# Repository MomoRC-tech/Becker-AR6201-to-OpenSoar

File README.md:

# ✈️ Wi-Fi Bridge: Glider Avionics to OpenSoar

<p align="center">
  
</p>

A small ESP32 box in the glider collects data from the cockpit instruments and sends it over Wi-Fi to OpenSoar on a phone or tablet. No cables run to the phone.

<p align="center">
<a href="docs/manual/user-manual.md"><picture><source media="(prefers-color-scheme: dark)" srcset="docs/images/nav/card-use-dark.svg"></picture></a>
<a href="docs/hardware/build-guide.md"><picture><source media="(prefers-color-scheme: dark)" srcset="docs/images/nav/card-build-dark.svg"></picture></a>
<a href="docs/README.md"><picture><source media="(prefers-color-scheme: dark)" srcset="docs/images/nav/card-reference-dark.svg"></picture></a>
</p>

---

## 1. 🎯 What it does

| Device | What you get in OpenSoar |
| --- | --- |
| 📈 Glider computer: Zander ZS1 | Flight and navigation data |
| 📡 Collision warning: Classic FLARM | Traffic and position |
| 📻 Radio: Becker AR6201 | Dedicated TCP port, verified with a bench loop. The stock OpenSoar driver is selected for the [remaining radio checks](docs/project/open-items.md#software-and-acceptance) |

Check and set it up from the phone's browser: live status per device, settings, a data monitor and a log ([web pages](docs/manual/user-manual.md#web-pages)).

<br clear="right">

---

## 2. 🚦 Status

> [!NOTE]
> **Status:** bench hardware bring-up is complete. Firmware 0.5.29 passed the hotspot phone reconnect, Becker loop and one-hour forwarding checks. [Remaining bench checks](docs/project/roadmap.md#firmware-plan)

---

## 3. ⚠️ Safety

> [!WARNING]
> Keep aircraft equipment disconnected during bench checks. Aircraft connection requires separate approval and verification of the installed wiring and radio revision. The existing installation stays untouched as a backup.

Working on the repository? Read the [work instructions](AGENTS.md) first.

---

<kbd>[⬆️ Back to top](#top)</kbd>

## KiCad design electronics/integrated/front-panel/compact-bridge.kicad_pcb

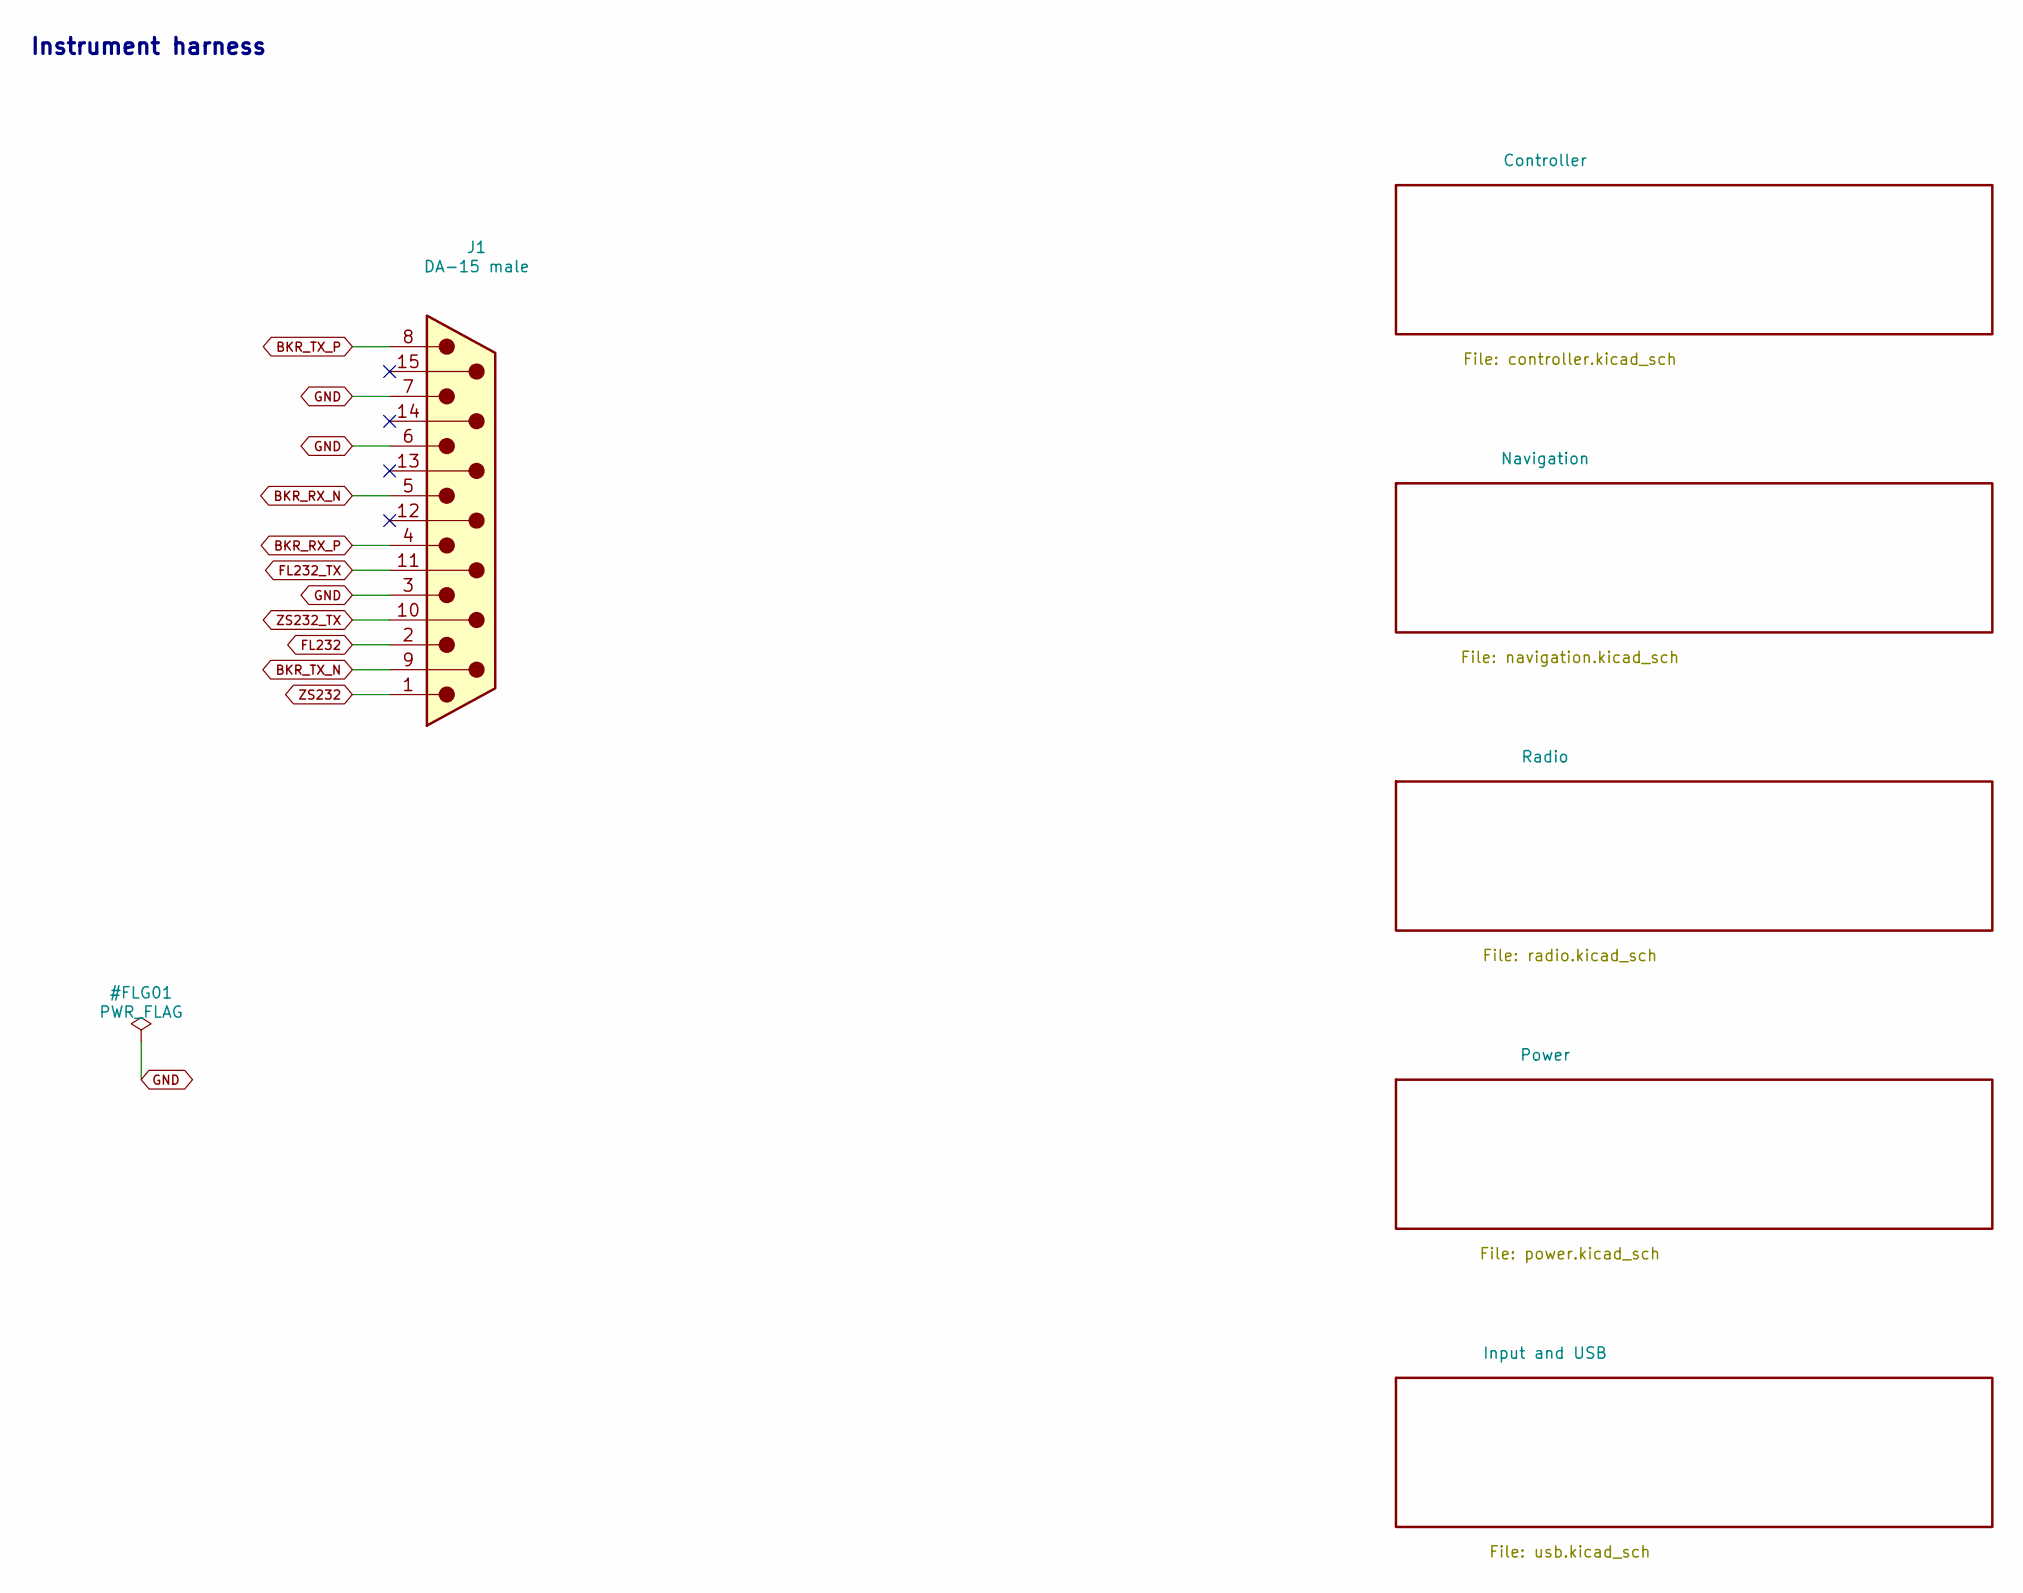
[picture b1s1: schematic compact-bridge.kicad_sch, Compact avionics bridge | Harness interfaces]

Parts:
J1: DA-15 male; Amphenol_D15P33E4GV00LF; MPN D15P33E4GV00LF; LCSC C3139986

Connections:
BKR_RX_N: J1.5; also elsewhere on the board
BKR_RX_P: J1.4; also elsewhere on the board
BKR_TX_N: J1.9; also elsewhere on the board
BKR_TX_P: J1.8; also elsewhere on the board
FL232: J1.2; also elsewhere on the board
FL232_TX: J1.11 (P111); also elsewhere on the board
GND: J1.3, J1.6, J1.7; also elsewhere on the board
ZS232: J1.1; also elsewhere on the board
ZS232_TX: J1.10; also elsewhere on the board

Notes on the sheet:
Instrument harness

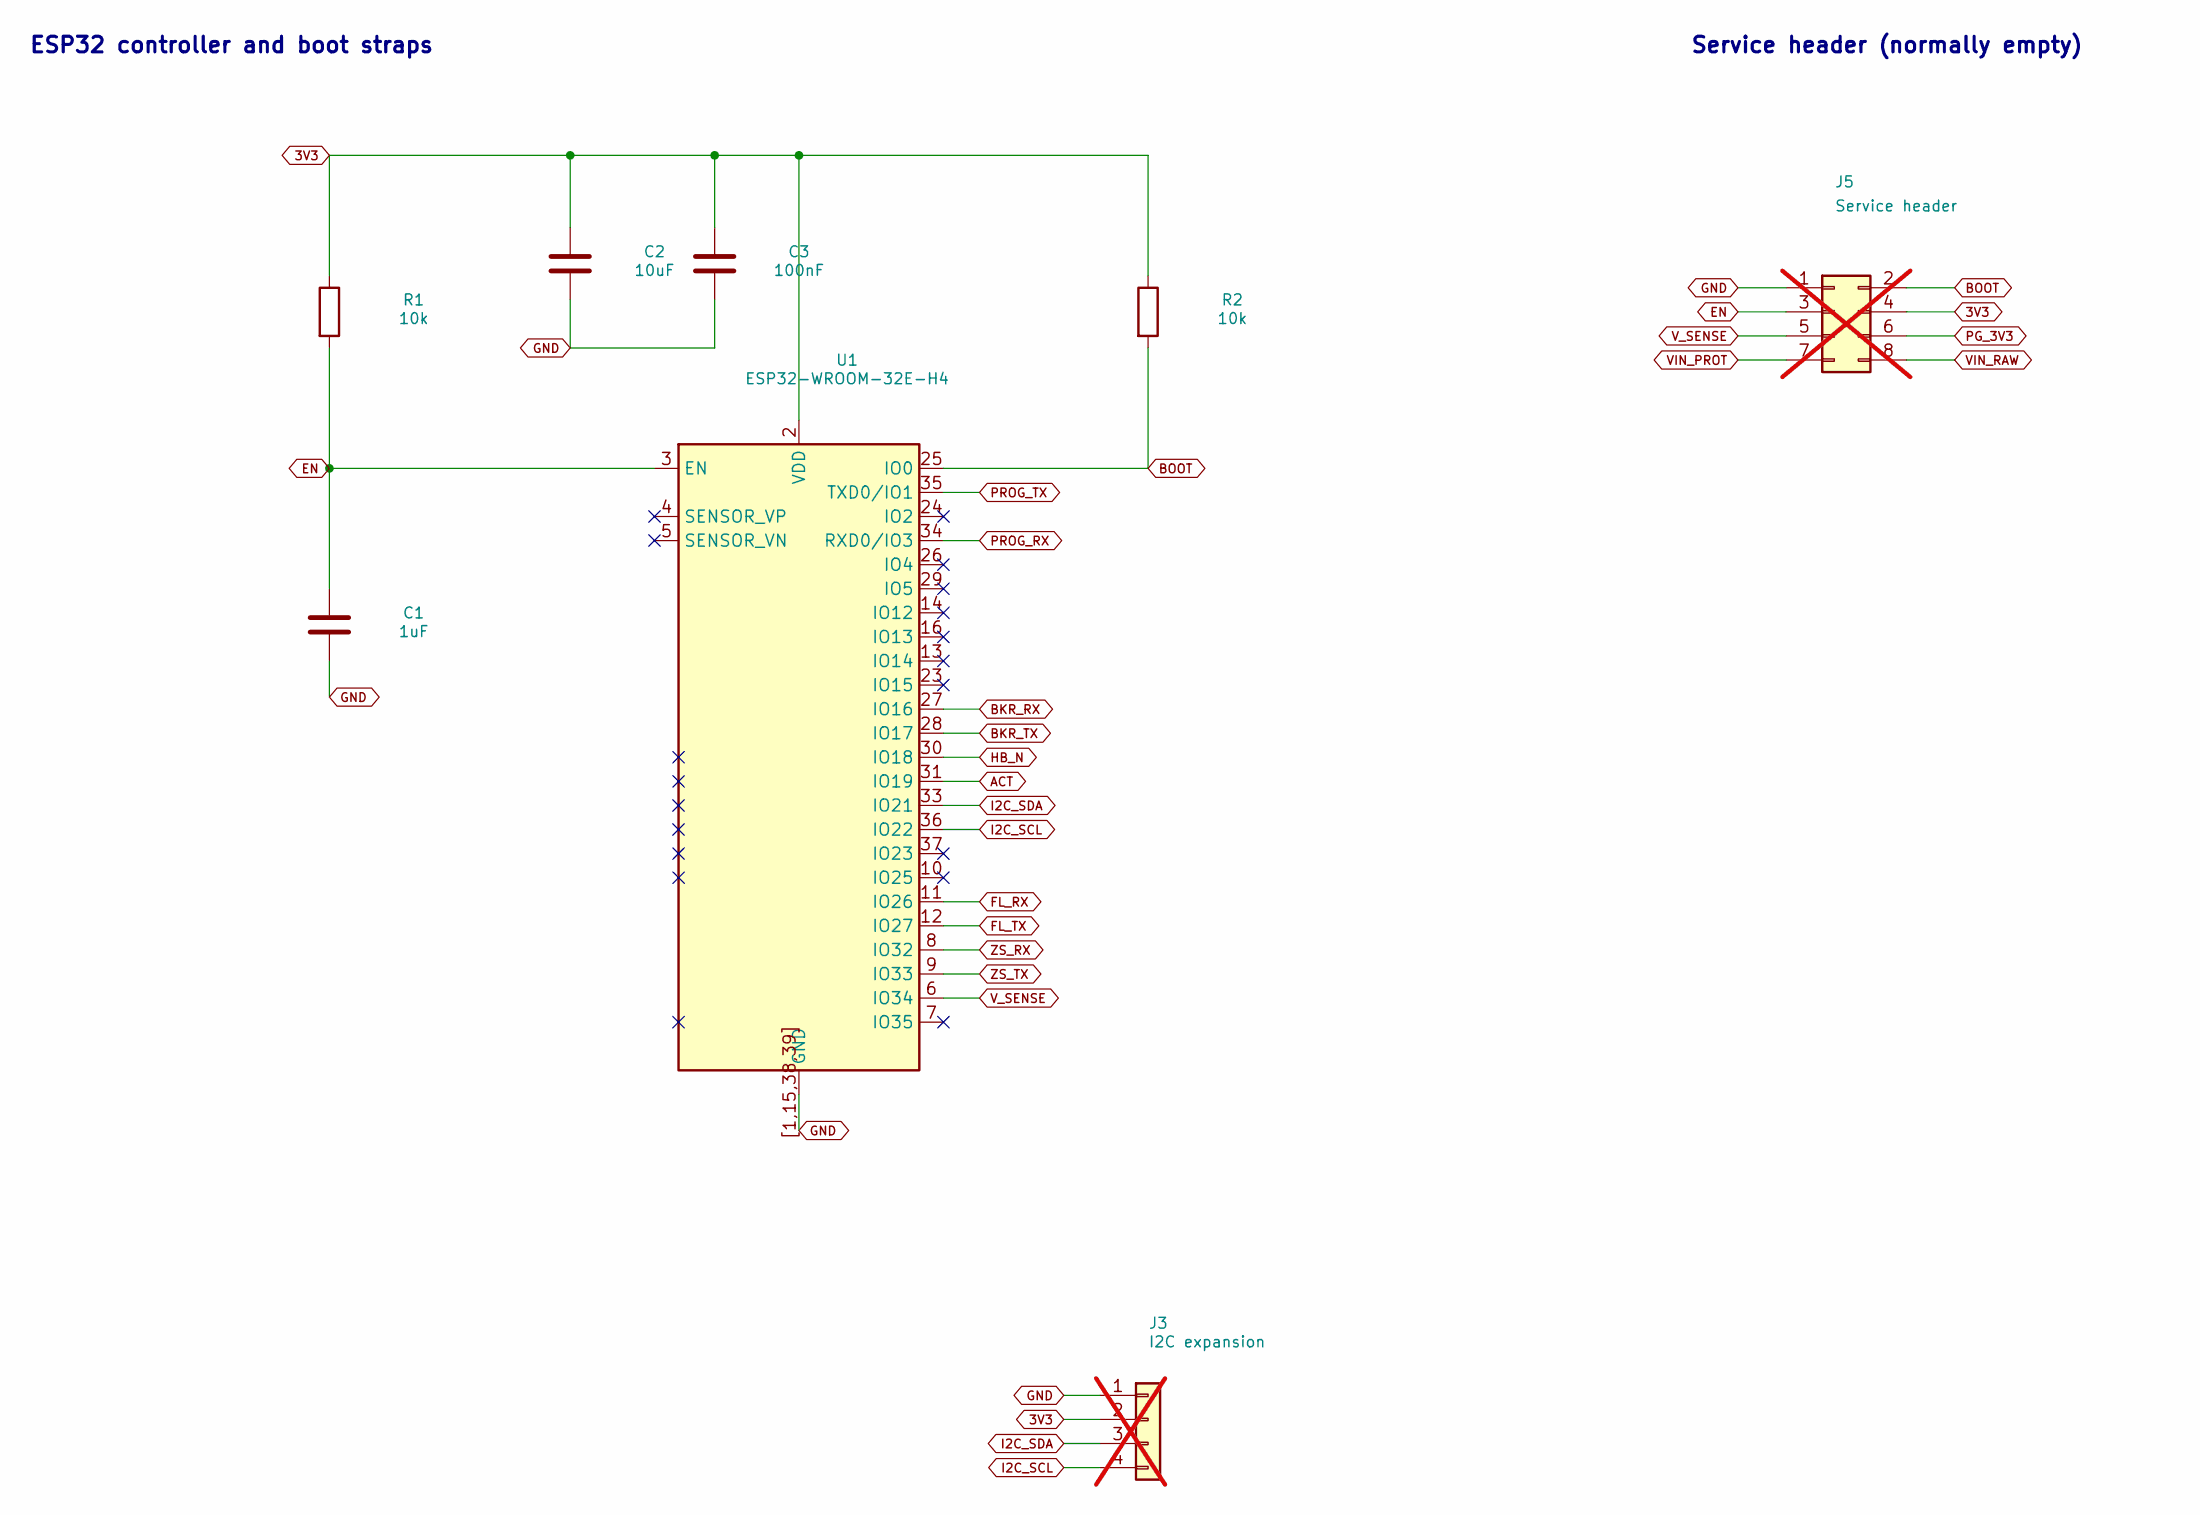
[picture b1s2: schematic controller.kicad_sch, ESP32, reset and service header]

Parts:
C1: 1uF; C_0603_1608Metric; MPN CC0603KRX7R8BB105; LCSC C106858
C2: 10uF; C_0805_2012Metric; MPN CL21A106KAYNNNE; LCSC C15850
C3: 100nF; C_0603_1608Metric; MPN CC0603KRX7R9BB104; LCSC C14663
J3: I2C expansion; PinHeader_1x04_P2.54mm_Vertical; not fitted
J5: Service header; PinHeader_2x04_P2.54mm_Vertical; not fitted
R1, R2: 10k; R_0603_1608Metric; MPN 0603WAF1002T5E; LCSC C25804
U1: ESP32-WROOM-32E-H4; ESP32-WROOM-32E-Edge; MPN ESP32-WROOM-32E-H4; LCSC C3013935

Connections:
3V3: C2.1, C3.1, J3.2, J5.4, R1.1, R2.1, U1.2 (VDD); also elsewhere on the board
ACT: U1.31 (IO19); also elsewhere on the board
BKR_RX: U1.27 (IO16); also elsewhere on the board
BKR_TX: U1.28 (IO17); also elsewhere on the board
BOOT: J5.2, R2.2, U1.25 (IO0)
EN: C1.1, J5.3, R1.2, U1.3 (EN)
FL_RX: U1.11 (IO26); also elsewhere on the board
FL_TX: U1.12 (IO27); also elsewhere on the board
GND: C1.2, C2.2, C3.2, J3.1, J5.1, U1.1 (GND), U1.15 (GND), U1.38 (GND), U1.39 (GND), U1.[1,15,38,39] (GND); also elsewhere on the board
HB_N: U1.30 (IO18); also elsewhere on the board
I2C_SCL: J3.4, U1.36 (IO22)
I2C_SDA: J3.3, U1.33 (IO21)
PG_3V3: J5.6; also elsewhere on the board
PROG_RX: U1.34 (RXD0/IO3); also elsewhere on the board
PROG_TX: U1.35 (TXD0/IO1); also elsewhere on the board
VIN_PROT: J5.7; also elsewhere on the board
VIN_RAW: J5.8; also elsewhere on the board
V_SENSE: J5.5, U1.6 (IO34); also elsewhere on the board
ZS_RX: U1.8 (IO32); also elsewhere on the board
ZS_TX: U1.9 (IO33); also elsewhere on the board

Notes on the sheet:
ESP32 controller and boot straps
Service header (normally empty)

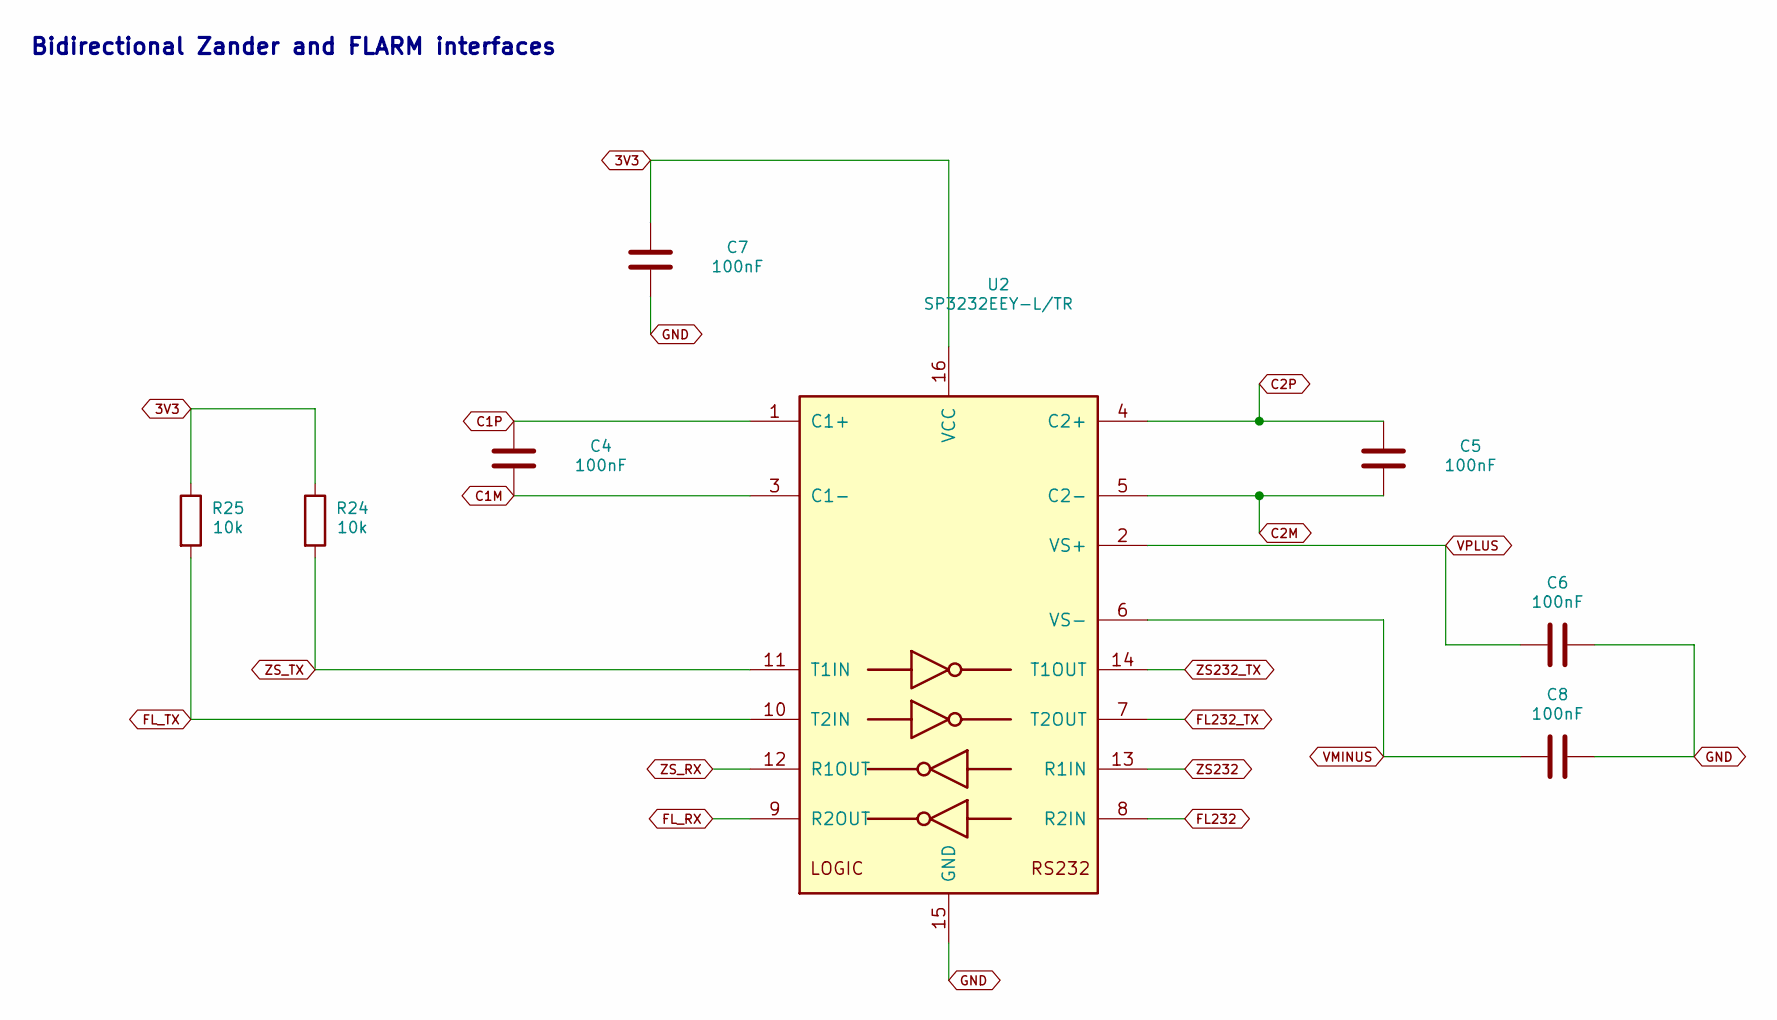
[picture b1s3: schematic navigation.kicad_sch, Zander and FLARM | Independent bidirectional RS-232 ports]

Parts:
C4, C5, C6, C7, C8: 100nF; C_0603_1608Metric; MPN CC0603KRX7R9BB104; LCSC C14663
R24, R25: 10k; R_0603_1608Metric; MPN 0603WAF1002T5E; LCSC C25804
U2: SP3232EEY-L/TR; TSSOP-16_4.4x5mm_P0.65mm; MPN SP3232EEY-L/TR; LCSC C13482

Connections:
3V3: C7.1, R24.1, R25.1, U2.16 (VCC); also elsewhere on the board
C1M: C4.2, U2.3 (C1-)
C1P: C4.1, U2.1 (C1+)
C2M: C5.2, U2.5 (C2-)
C2P: C5.1, U2.4 (C2+)
FL232: U2.8 (R2IN); also elsewhere on the board
FL232_TX: U2.7 (T2OUT); also elsewhere on the board
FL_RX: U2.9 (R2OUT); also elsewhere on the board
FL_TX: R25.2, U2.10 (T2IN); also elsewhere on the board
GND: C6.2, C7.2, C8.1, U2.15 (GND); also elsewhere on the board
VMINUS: C8.2, U2.6 (VS-)
VPLUS: C6.1, U2.2 (VS+)
ZS232: U2.13 (R1IN); also elsewhere on the board
ZS232_TX: U2.14 (T1OUT); also elsewhere on the board
ZS_RX: U2.12 (R1OUT); also elsewhere on the board
ZS_TX: R24.2, U2.11 (T1IN); also elsewhere on the board

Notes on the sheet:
Bidirectional Zander and FLARM interfaces

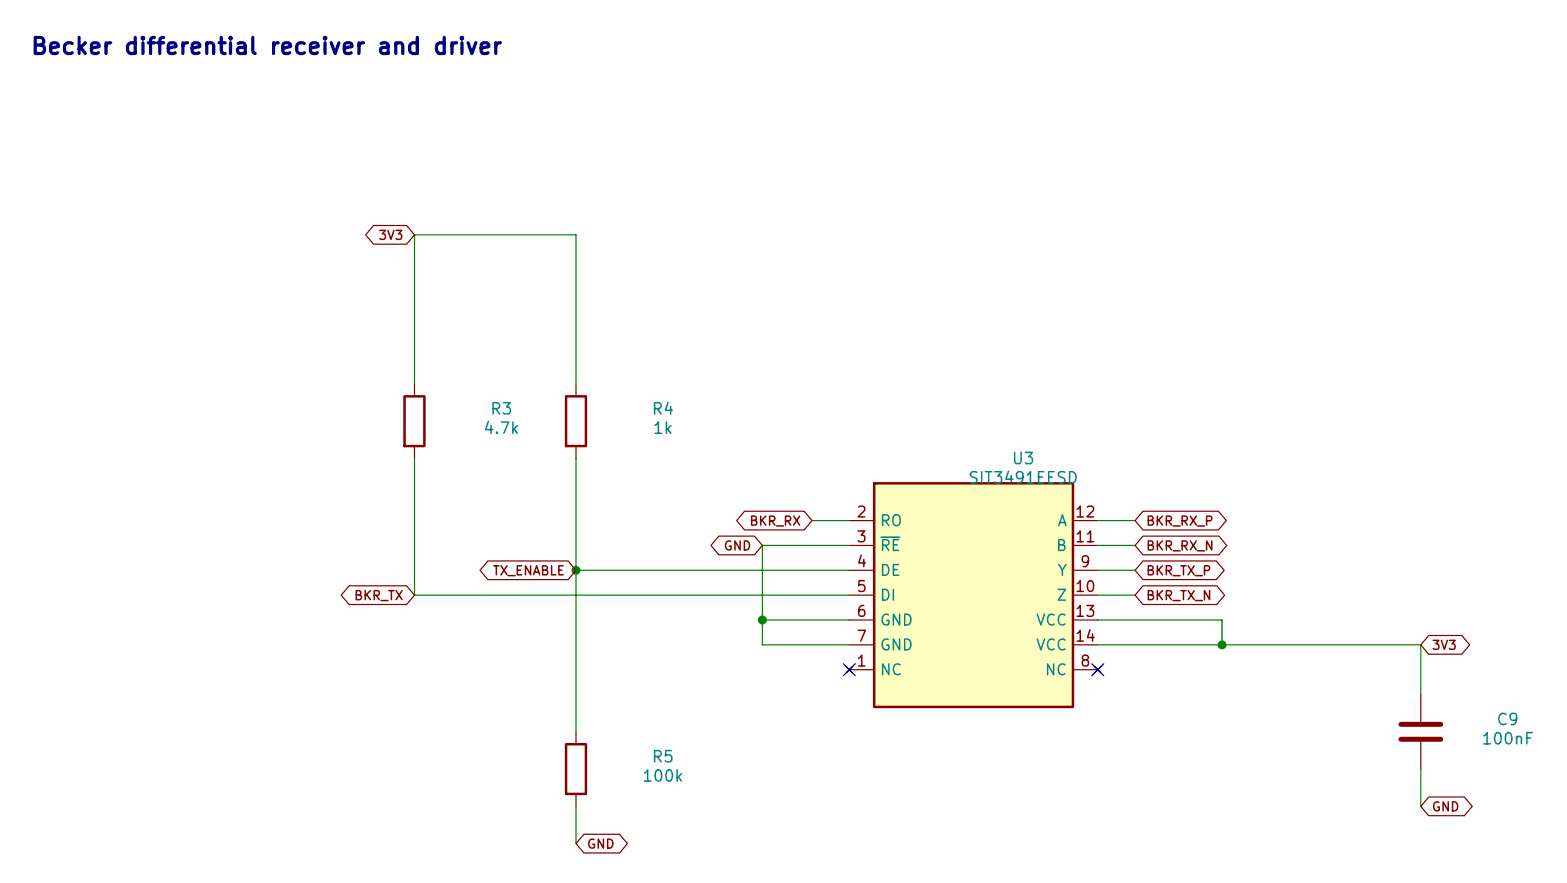
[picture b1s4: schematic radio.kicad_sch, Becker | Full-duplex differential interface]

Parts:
C9: 100nF; C_0603_1608Metric; MPN CC0603KRX7R9BB104; LCSC C14663
R3: 4.7k; R_0603_1608Metric; MPN 0603WAF4701T5E; LCSC C23162
R4: 1k; R_0603_1608Metric; MPN 0603WAF1001T5E; LCSC C21190
R5: 100k; R_0603_1608Metric; MPN 0603WAF1003T5E; LCSC C25803
U3: SIT3491EESD; SOIC-14_3.9x8.7mm_P1.27mm; MPN SIT3491EESD; LCSC C496617

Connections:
3V3: C9.1, R3.1, R4.1, U3.13 (VCC), U3.14 (VCC); also elsewhere on the board
BKR_RX: U3.2 (RO); also elsewhere on the board
BKR_RX_N: U3.11 (B); also elsewhere on the board
BKR_RX_P: U3.12 (A); also elsewhere on the board
BKR_TX: R3.2, U3.5 (DI); also elsewhere on the board
BKR_TX_N: U3.10 (Z); also elsewhere on the board
BKR_TX_P: U3.9 (Y); also elsewhere on the board
GND: C9.2, R5.2, U3.3 (~RE), U3.6 (GND), U3.7 (GND); also elsewhere on the board
TX_ENABLE: R4.2, R5.1, U3.4 (DE)

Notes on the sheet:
Becker differential receiver and driver

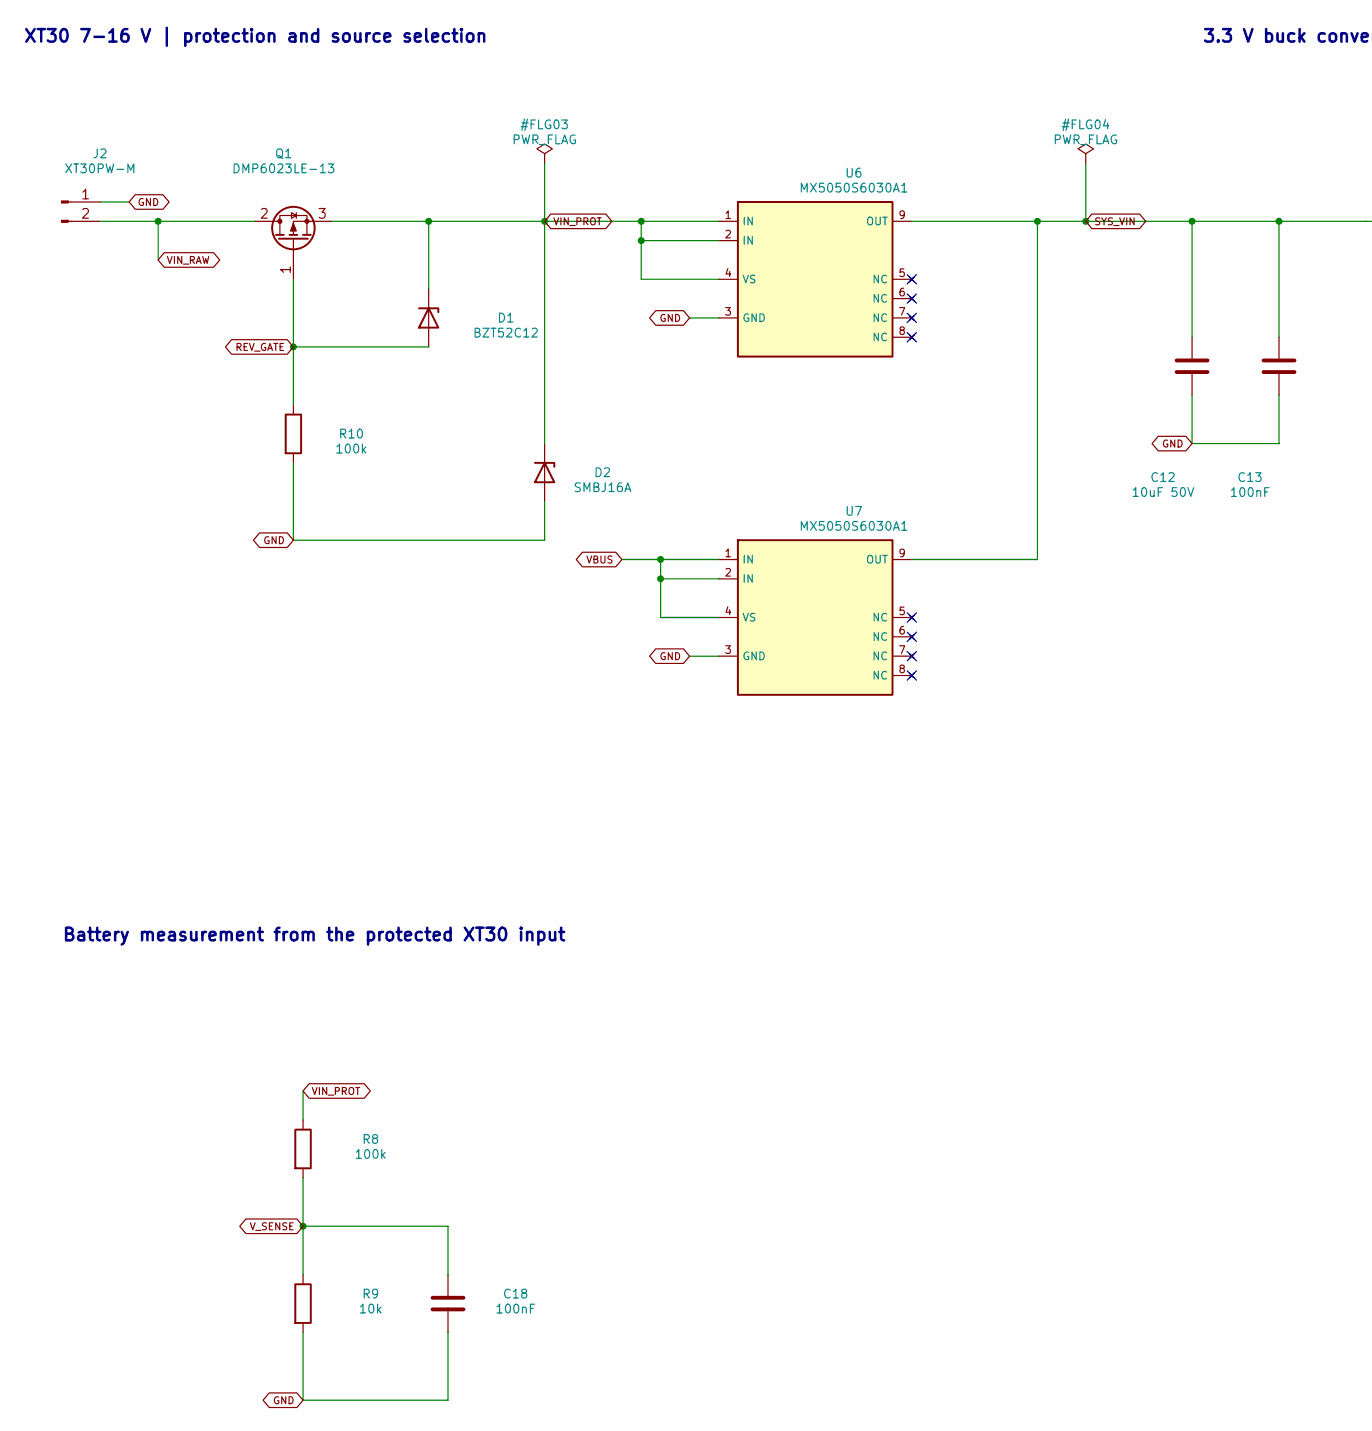
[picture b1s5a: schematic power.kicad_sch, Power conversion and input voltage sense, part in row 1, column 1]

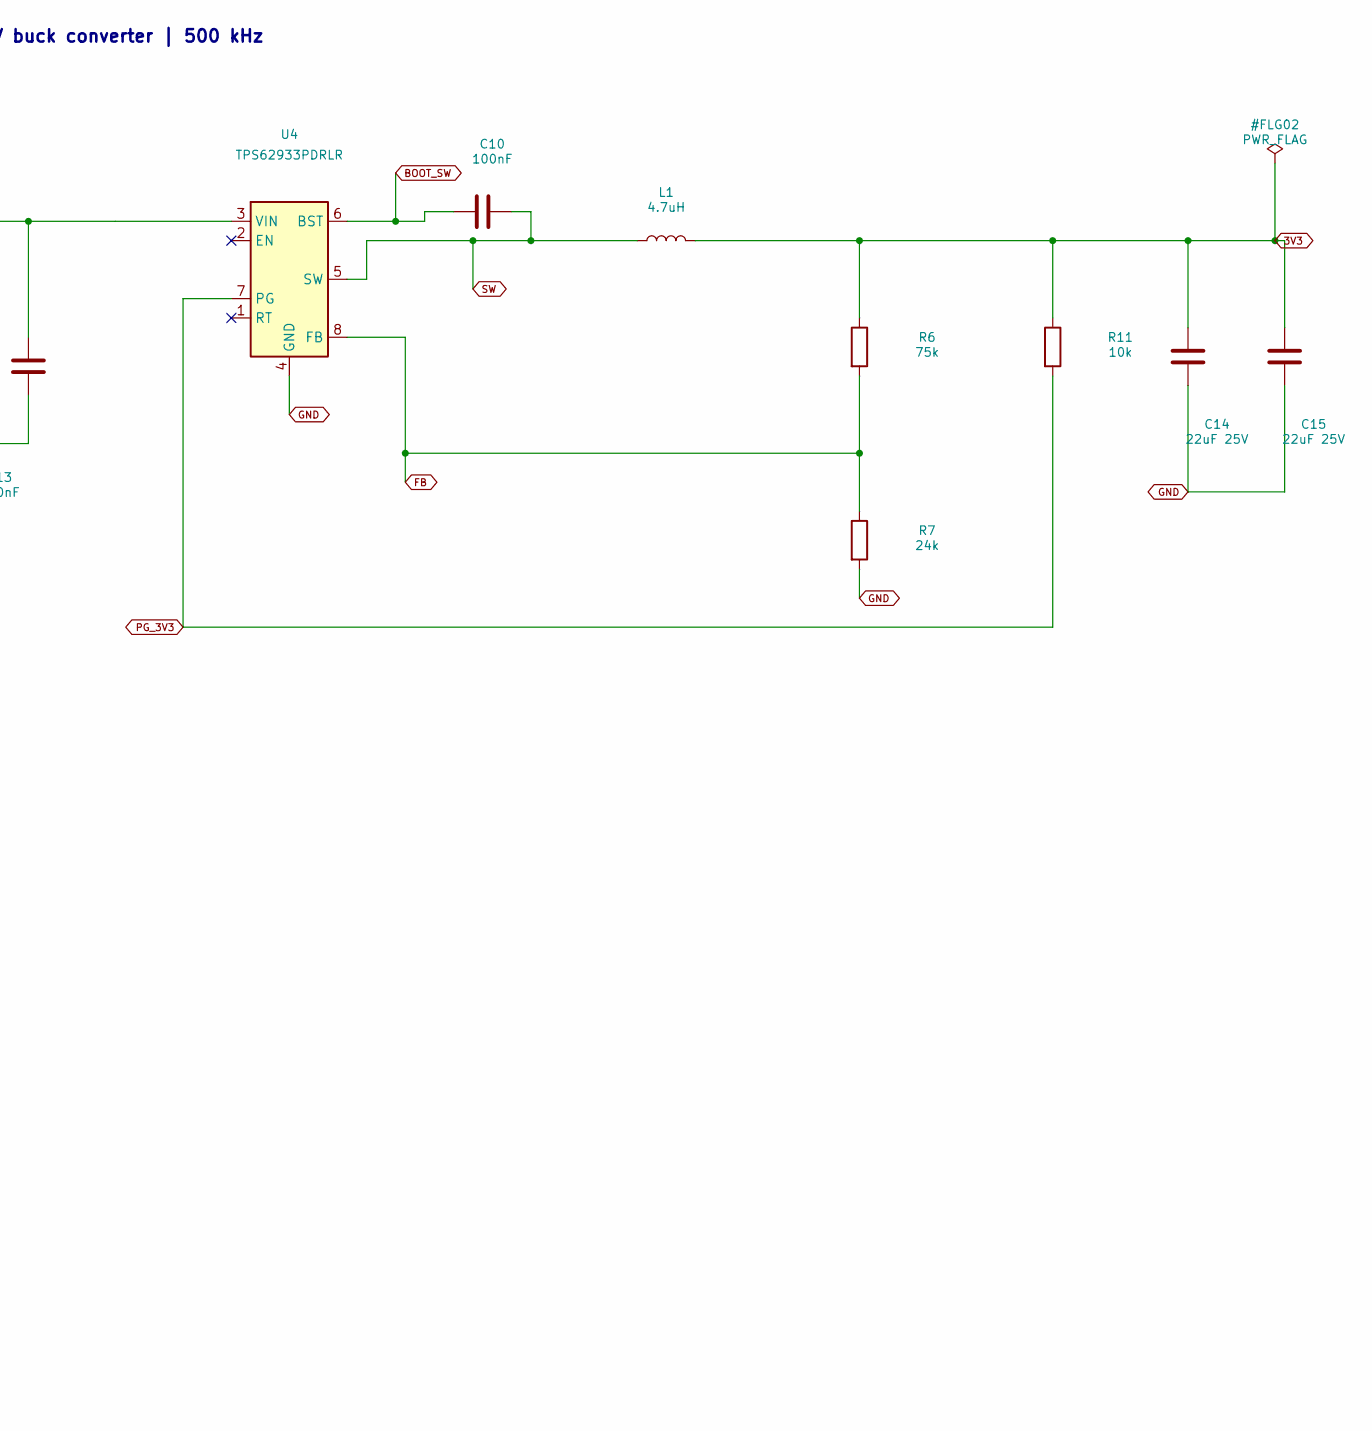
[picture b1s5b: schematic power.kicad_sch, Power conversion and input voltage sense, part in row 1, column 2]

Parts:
C10, C13, C18: 100nF; C_0603_1608Metric; MPN CC0603KRX7R9BB104; LCSC C14663
C12: 10uF 50V; C_1206_3216Metric; MPN CL31A106KBHNNNE; LCSC C13585
C14, C15: 22uF 25V; C_1206_3216Metric; MPN CL31A226KAHNNNE; LCSC C12891
D1: BZT52C12; D_SOD-123; MPN BZT52C12; LCSC C19077410
D2: SMBJ16A; D_SMB; MPN SMBJ16A; LCSC C151254
J2: XT30PW-M; AMASS_XT30PW-M; MPN XT30PW-M30.G.Y; LCSC C431092
L1: 4.7uH; L_Sunlord_MWSA0603S; MPN MWSA0603S-4R7MT; LCSC C408447
Q1: DMP6023LE-13; SOT-223-3_TabPin2; MPN DMP6023LE-13; LCSC C154901
R6: 75k; R_0603_1608Metric; MPN 0603WAF7502T5E; LCSC C23242
R7: 24k; R_0603_1608Metric; MPN 0603WAF2402T5E; LCSC C23352
R8, R10: 100k; R_0603_1608Metric; MPN 0603WAF1003T5E; LCSC C25803
R9, R11: 10k; R_0603_1608Metric; MPN 0603WAF1002T5E; LCSC C25804
U4: TPS62933PDRLR; SOT-583-8; MPN TPS62933PDRLR; LCSC C5219254
U6, U7: MX5050S6030A1; SOIC-8-1EP_3.9x4.9mm_P1.27mm_EP2.41x3.3mm; MPN MX5050S6030A1; LCSC C54800033

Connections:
3V3: C14.1, C15.1, L1.2, R6.1, R11.1; also elsewhere on the board
BOOT_SW: C10.1, U4.6 (BST)
FB: R6.2, R7.1, U4.8 (FB)
GND: C12.2, C13.2, C14.2, C15.2, C18.2, D2.2 (A), J2.1, R7.2, R9.2, R10.2, U4.4 (GND), U6.3 (GND), U7.3 (GND); also elsewhere on the board
PG_3V3: R11.2, U4.7 (PG); also elsewhere on the board
REV_GATE: D1.2 (A), Q1.1 (G), R10.1
SW: C10.2, L1.1, U4.5 (SW)
SYS_VIN: C12.1, C13.1, U4.3 (VIN), U6.9 (OUT), U7.9 (OUT)
VBUS: U7.1 (IN), U7.2 (IN), U7.4 (VS); also elsewhere on the board
VIN_PROT: D1.1 (K), D2.1 (K), Q1.3 (S), R8.1, U6.1 (IN), U6.2 (IN), U6.4 (VS); also elsewhere on the board
VIN_RAW: J2.2, Q1.2 (D); also elsewhere on the board
V_SENSE: C18.1, R8.2, R9.1; also elsewhere on the board

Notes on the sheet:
XT30 7-16 V | protection and source selection
3.3 V buck converter | 500 kHz
Battery measurement from the protected XT30 input

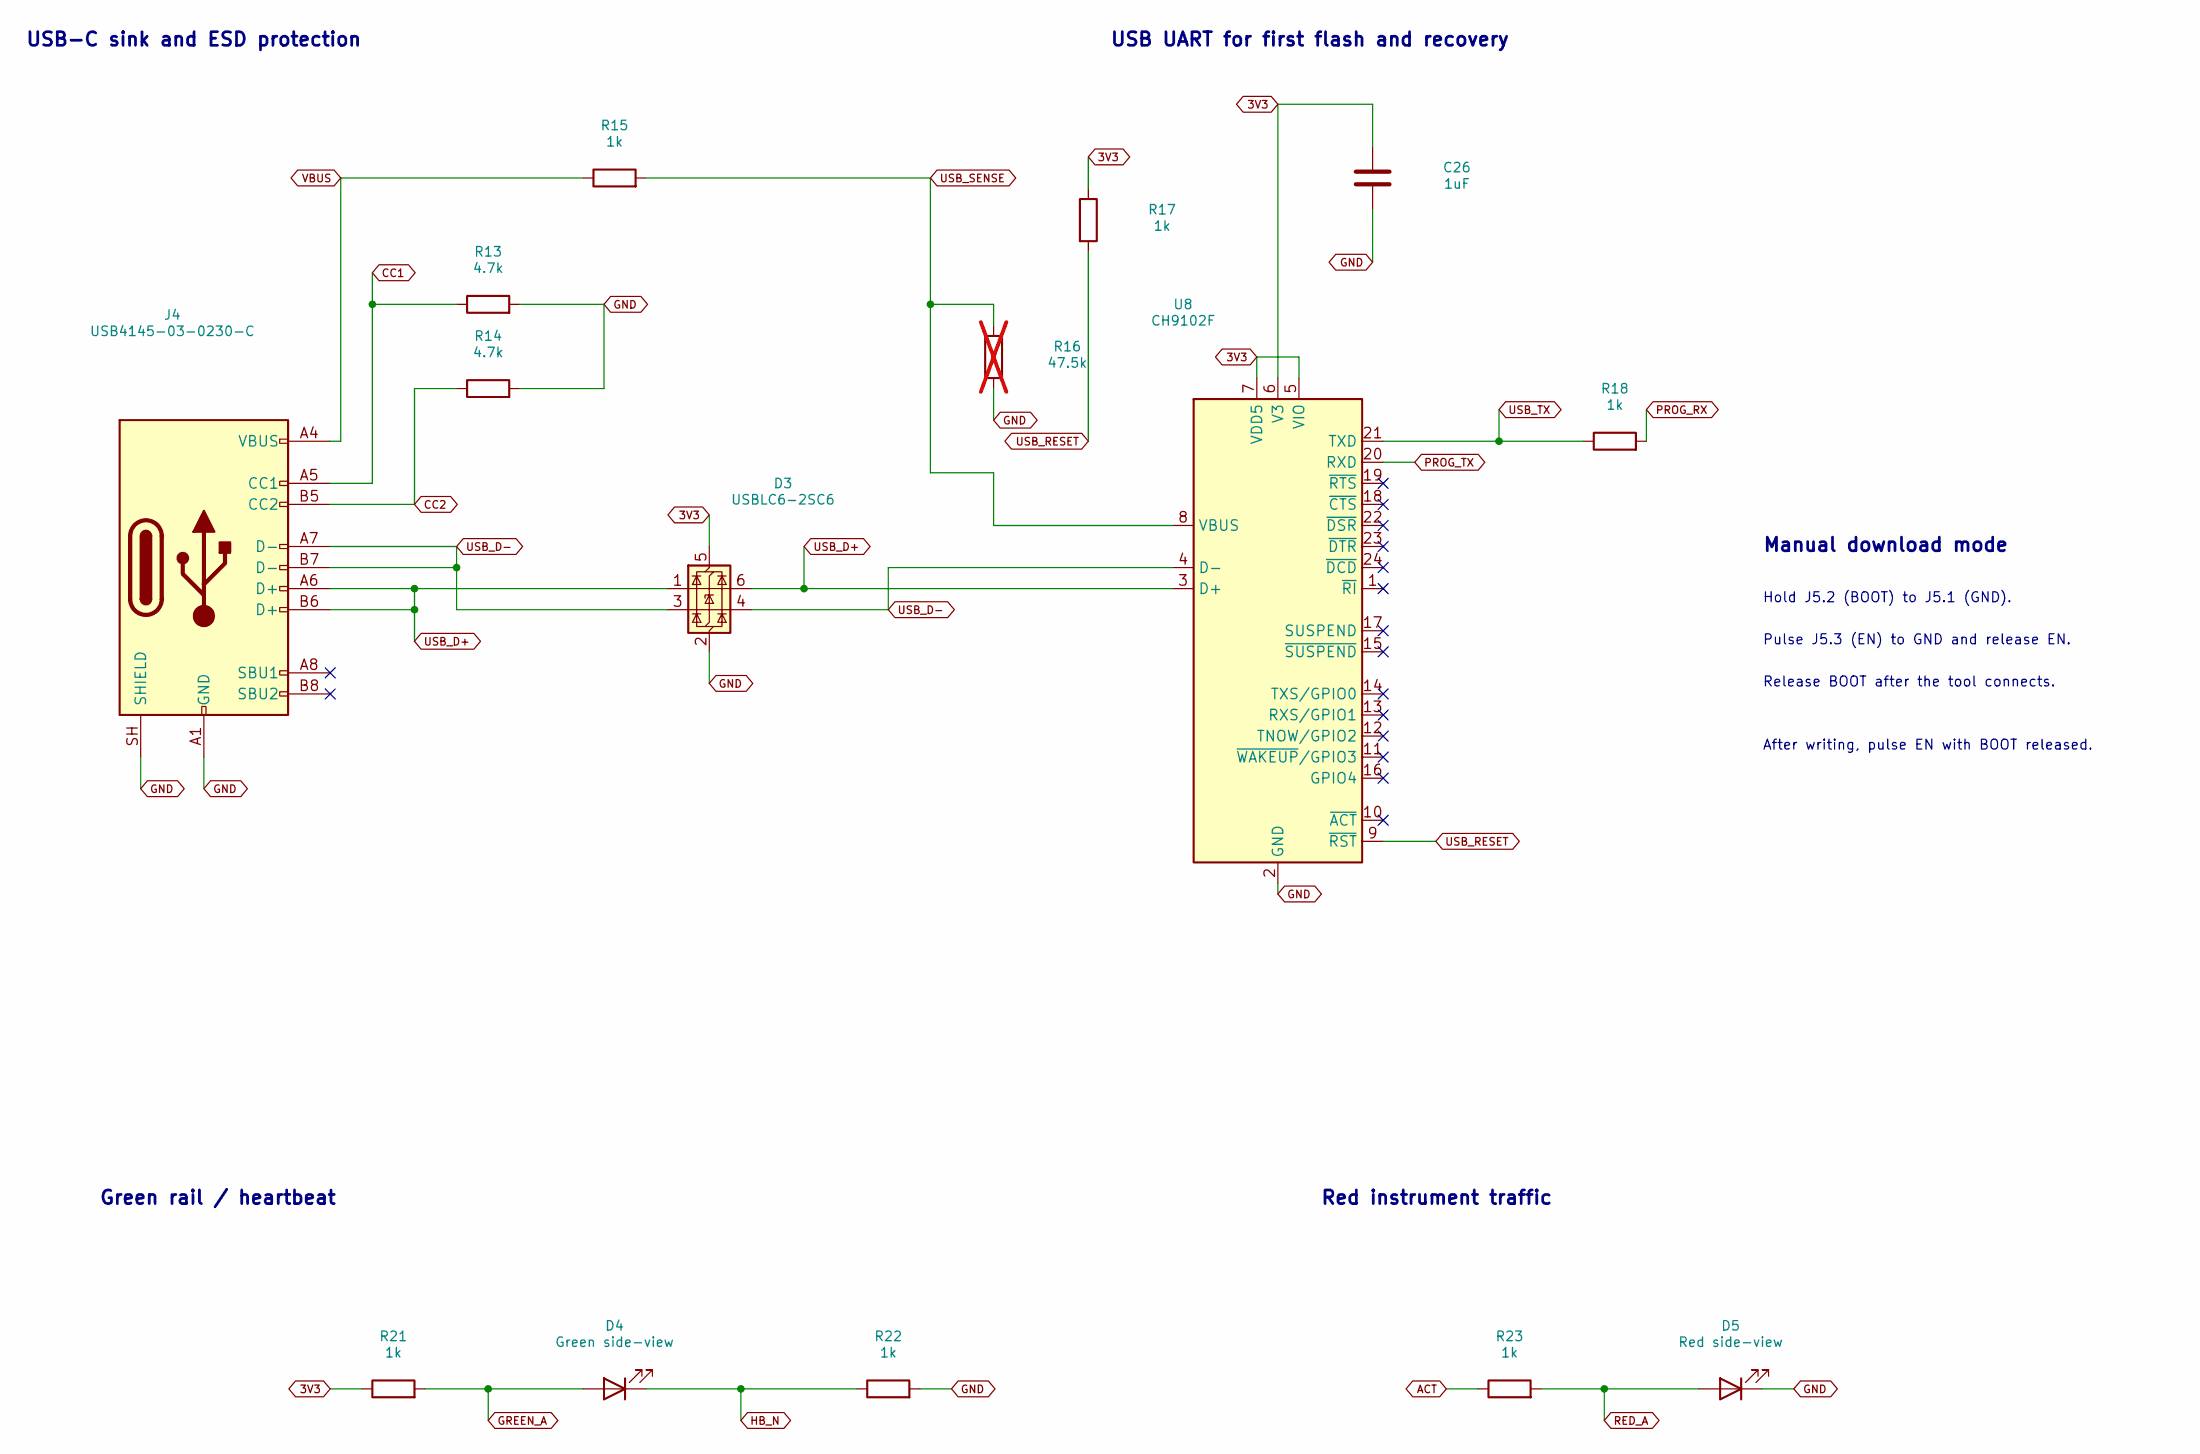
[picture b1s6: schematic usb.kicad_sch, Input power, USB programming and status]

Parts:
C26: 1uF; C_0603_1608Metric; MPN CC0603KRX7R8BB105; LCSC C106858
D3: USBLC6-2SC6; SOT-23-6; MPN USBLC6-2SC6; LCSC C7519
D4: Green side-view; LiteOn_LTST-S270; MPN LTST-S270KGKT; LCSC C125113
D5: Red side-view; LiteOn_LTST-S270; MPN LTST-S270KRKT; LCSC C125114
J4: USB4145-03-0230-C; GCT_USB4145; MPN USB4145-03-0230-C; LCSC C5291559
R13, R14: 4.7k; R_0603_1608Metric; MPN 0603WAF4701T5E; LCSC C23162
R15, R17, R18, R21, R22, R23: 1k; R_0603_1608Metric; MPN 0603WAF1001T5E; LCSC C21190
R16: 47.5k; R_0603_1608Metric; MPN 0603WAF4752T5E; LCSC C23061; not fitted
U8: CH9102F; QFN-24-1EP_4x4mm_P0.5mm_EP2.6x2.6mm; MPN CH9102F; LCSC C2858418

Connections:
3V3: C26.1, D3.5 (VBUS), R17.1, R21.1, U8.5 (VIO), U8.6 (V3), U8.7 (VDD5); also elsewhere on the board
ACT: R23.1; also elsewhere on the board
CC1: J4.A5 (CC1), R13.1
CC2: J4.B5 (CC2), R14.1
GND: C26.2, D3.2 (GND), D5.1 (K), J4.A1 (GND), J4.A12 (GND), J4.B1 (GND), J4.B12 (GND), J4.SH (SHIELD), R13.2, R14.2, R16.2, R22.2, U8.2 (GND), U8.25 (GND); also elsewhere on the board
GREEN_A: D4.2 (A), R21.2
HB_N: D4.1 (K), R22.1; also elsewhere on the board
PROG_RX: R18.2; also elsewhere on the board
PROG_TX: U8.20 (RXD); also elsewhere on the board
RED_A: D5.2 (A), R23.2
USB_D+: D3.1 (I/O1), D3.6 (I/O1), J4.A6 (D+), J4.B6 (D+), U8.3 (D+)
USB_D-: D3.3 (I/O2), D3.4 (I/O2), J4.A7 (D-), J4.B7 (D-), U8.4 (D-)
USB_RESET: R17.2, U8.9 (~RST)
USB_SENSE: R15.2, R16.1, U8.8 (VBUS)
USB_TX: R18.1, U8.21 (TXD)
VBUS: J4.A4 (VBUS), J4.A9 (VBUS), J4.B4 (VBUS), J4.B9 (VBUS), R15.1; also elsewhere on the board

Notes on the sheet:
USB-C sink and ESD protection
USB UART for first flash and recovery
Green rail / heartbeat
Red instrument traffic
Manual download mode
Hold J5.2 (BOOT) to J5.1 (GND).
Pulse J5.3 (EN) to GND and release EN.
Release BOOT after the tool connects.
After writing, pulse EN with BOOT released.

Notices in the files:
parts and their libraries:
ESP32-WROOM-32E. KiCad Library Team, RF_Module:ESP32-WROOM-32E, KiCad 10. Pin-1 silk mark moved 0.34 mm onto the PCB and 0.70 mm outward. CC-BY-SA-4.0 with KiCad exception. See KICAD-LIBRARY-LICENSE.md.
